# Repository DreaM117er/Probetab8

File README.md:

# Probetab8

|||
|--|--|
|||

## 說明

Probetab8是一把在設計途中不斷地向Google Gemini諮詢電路學知識的一把迷你鍵盤，是我用來進一步地學習電路學的一個巨大突破的成果。

這把鍵盤有以下幾個特點：
1. 晶片核心爲RP2040，全引腳輸出。
2. 可以燒錄RP2040 Debug Probe官方的韌體。
3. 可以按照我設計的佈局設置需要的功能：4+4顆按鍵、4按鍵+1旋鈕、2旋鈕。
4. 搭載Azoteq TPS65觸控板。
5. QMK/VIAL韌體。

## 使用材料

|||
|--|--|

### 電子元件

|類型|名稱|數量|封裝|備註|Reference|
|--|--|--|--|--|--|
|MCU|RP2040|1|QFN-56|-|U3|
|ESD|SRV05-4|1|SOT-23-6|-|U1|
|LDO|RT9013-33GB|1|SOT-23-5|-|U2|
|QSPI|W25Q128JVS|1|SOIC-8|-|U4|
|Resonator|Crystal|1|SMD-3225-4Pin|-|Y1|
|Receptacle|USB-C|1|-|16Pin|-|
|Fuse|6V, 500mA|1|0805|-|F1|
|SW|-|1|SPST_TL3342|BOOT||
|Capacitor|1uF|4|0603|-|C1, C2, C8, C16|
|Capacitor|15pF|2|0603|-|C3, C4|
|Capacitor|100nF|10|0603|-|C5-C7, C9-C15|
|Resistor|5.1K|2|0603|-|R1, R2|
|Resistor|27R|2|0603|-|R3, R4|
|Resistor|10K|2|0603|-|R5, R7|
|Resistor|1K|1|0603|-|R6|
|Resistor|470R|2|0603|-|R8, R9|
|Resistor|220R|1|0603|-|R10|
|Module|TPS65-201A-S|1|-|-|-|
|Cable|FFC-0.5mm|1|6Pin|L: 100mm|-|
|Socket|FFC-0.5mm|1|FH12-6S-0.5SH 6Pin|-|-|
|RED|LED|3|0603|After R8-10|-|

### 機構元件

|名稱|規格|數量|備註|
|--|--|--|--|
|Screw|M2x4mm|4|扁頭|
|Screw|M2x6mm|2|扁頭|
|Screw|M2x8mm|2|扁頭|
|Case|上蓋|1|-|
|Case|下蓋|1|-|
|Feets|8x1mm|4|矽膠腳貼|

### 自由選擇

|名稱|規格|數量|備註|
|--|--|--|--|
|按鍵|Choc v1, GLP1.0-2.0|0-8|-|
|鍵帽|Choc v1, MX stem for LP|0-8|-|
|編碼器|EC-11|0-2|L: 10mm、A: 5.5-5.0mm, 半軸 D型|

## 注意事項

- 不提供CSV給大家使用，如果需要PCBA，請自行修改PCB檔案。因爲這把鍵盤屬於純手工焊接，挑戰自己的焊接技巧，成果就是你的。
- 外殼上蓋有分4種，分別應對自由選擇的元件使用，底殼通用。
- 外殼檔案及PCB檔案都開放給大家，要修正改造請按照開源相關規定，我就不再說明了。 
- 焊接的時候，特別注意預熱、加熱相關的技巧及熟悉度，以免燒壞MCU或是燙傷；還有注意環境通風。
- 關於Jumper：

    - Status LED：測試燈開關，測試沒問題可移除。
    - TPS65模組：RDY及RST，有使用這兩個引腳再焊接。

## 軟體工具

- Fusion。
- KiCAD 9.0.2。
- VScode。
- QMK、VIAL。
- Resberry官方Debug Probe韌體。

## 硬體工具

- TS-100、TS-101。
- MPH-30。
- FDM列印機。
- 萬用電表。

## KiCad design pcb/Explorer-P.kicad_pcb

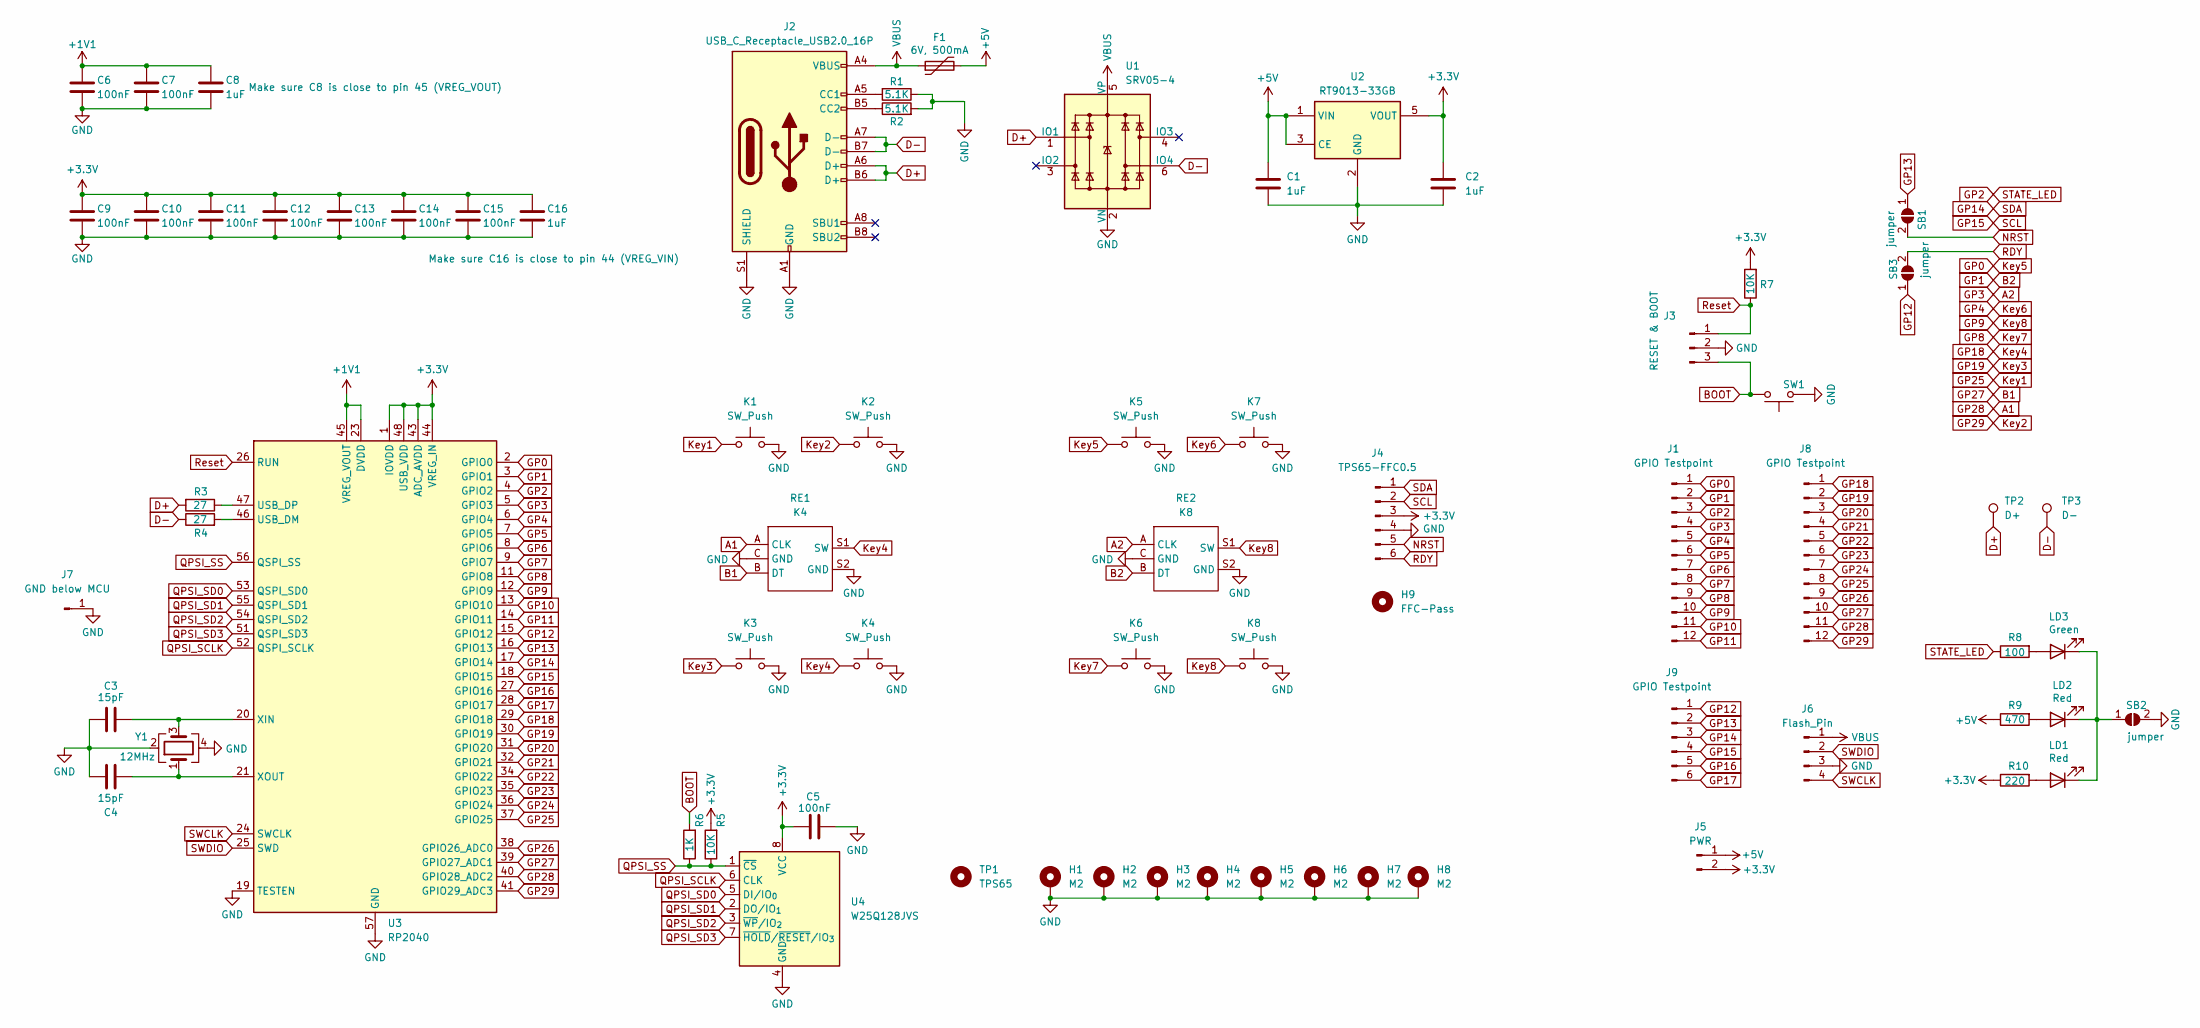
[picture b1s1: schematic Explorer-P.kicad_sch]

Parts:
C1, C2: 1uF; R_0603_1608Metric
C3, C4: 15pF; R_0603_1608Metric
C5: 100nF; R_0603_1608Metric
C6, C7, C9, C10, C11, C12, C13, C14, C15: 100nF; R_0603_1608Metric; MFR. Part # CL05B104KB54PNC
C8, C16: 1uF; R_0603_1608Metric; MFR. Part # CL05A105KA5NQNC
F1: 6V, 500mA; C_0805_2012Metric_Pad1.18x1.45mm_HandSolder; LCSC C269104
H1, H2, H3, H4, H5, H6, H7, H8: M2; MountingHole_2.2mm_M2_DIN965_Pad
H9: FFC-Pass; MountingHole_2.2mm_M2
J1, J8: GPIO Testpoint; Testpoint_2.54mm_01x12_1to2_Hole2Pad
J2: USB_C_Receptacle_USB2.0_16P; USB_C_Receptacle_G-Switch_GT-USB-7010ASV
J3: RESET & BOOT; PinHeader_1x03_P2.54mm_Vertical
J4: TPS65-FFC0.5; Hirose_FH12-6S-0.5SH_1x06-1MP_P0.50mm_Horizontal
J5: PWR; Testpoint_2.54mm_01x02_1to2_Hole2Pad
J6: Flash_Pin; PinHeader_1x04_P2.54mm_Vertical
J7: GND below MCU; MountingHole_2.2mm_M2_DIN965_Pad
J9: GPIO Testpoint; Testpoint_2.54mm_01x06_1to2_Hole2Pad
K1, K2, K3, K4, K5, K6, K7, K8: SW_Push; SW_Choc_GLP_KLP12_THT2
LD1, LD2: Red; LED_0603_1608Metric; MFR. Part # 19-217/GHC-YR1S2/3T; LCSC C72043
LD3: Green; LED_0603_1608Metric; MFR. Part # 19-217/GHC-YR1S2/3T; LCSC C72043
R1, R2: 5.1K; R_0603_1608Metric
R3, R4: 27; R_0603_1608Metric
R5, R7: 10K; R_0603_1608Metric
R6: 1K; R_0603_1608Metric
R8: 100; R_0603_1608Metric; MFR. Part # 0402WGF1001TCE
R9: 470; R_0603_1608Metric; MFR. Part # 0402WGF1001TCE
R10: 220; R_0603_1608Metric; MFR. Part # 0402WGF1001TCE
RE1: K4; RotaryEncoder_EC11
RE2: K8; RotaryEncoder_EC11
SB1, SB2, SB3: jumper; SolderJumper-2_P1.3mm_Open_TrianglePad1.0x1.5mm
SW1: BOOT; SW_SPST_TL3342
TP1: TPS65; Azoteq_TPS65_201A_S
TP2: D+; TestPoint_Pad_2.5x2.5mm
TP3: D-; TestPoint_Pad_2.5x2.5mm
U1: SRV05-4; SOT-23-6
U2: RT9013-33GB; SOT-23-5; LCSC C47773
U3: RP2040; QFN-56-1EP_7x7mm_P0.4mm_EP3.2x3.2mm; LCSC C2040
U4: W25Q128JVS; SOIC-8_5.3x5.3mm_P1.27mm; LCSC C97521
Y1: 12MHz; Crystal_SMD_3225-4Pin_3.2x2.5mm; LCSC C9002

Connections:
+1V1: C6.1, C7.1, C8.1, U3.23 (DVDD), U3.45 (VREG_VOUT), U3.50 (DVDD)
+3.3V: C2.1, C5.1, C9.1, C10.1, C11.1, C12.1, C13.1, C14.1, C15.1, C16.1, J4.3, J5.2, R5.2, R7.2, R10.1, U2.5 (VOUT), U3.1 (IOVDD), U3.10 (IOVDD), U3.22 (IOVDD), U3.33 (IOVDD), U3.42 (IOVDD), U3.43 (ADC_AVDD), U3.44 (VREG_IN), U3.48 (USB_VDD), U3.49 (IOVDD), U4.8 (VCC)
+5V: C1.2, F1.2, J5.1, R9.1, U2.1 (VIN), U2.3 (CE)
A1: J8.11, RE1.A (CLK), U3.40 (GPIO28_ADC2)
A2: J1.4, RE2.A (CLK), U3.5 (GPIO3)
B1: J8.10, RE1.B (DT), U3.39 (GPIO27_ADC1)
B2: J1.2, RE2.B (DT), U3.3 (GPIO1)
BOOT: J3.3, R6.2, SW1.2
D+: J2.A6 (D+), J2.B6 (D+), R3.2, TP2.1, U1.1 (IO1)
D-: J2.A7 (D-), J2.B7 (D-), R4.1, TP3.1, U1.6 (IO4)
GND: C1.1, C2.2, C3.2, C4.2, C5.2, C6.2, C7.2, C8.2, C9.2, C10.2, C11.2, C12.2, C13.2, C14.2, C15.2, C16.2, H1.1, H2.1, H3.1, H4.1, H5.1, H6.1, H7.1, H8.1, J2.A1 (GND), J2.A12 (GND), J2.B1 (GND), J2.B12 (GND), J2.S1 (SHIELD), J3.2, J4.4, J6.3, J7.1, K1.2, K2.2, K3.2, K4.2, K5.2, K6.2, K7.2, K8.2, R1.1, R2.2, RE1.C (GND), RE1.S2 (GND), RE2.C (GND), RE2.S2 (GND), SB2.2 (B), SW1.1, U1.2 (VN), U2.2 (GND), U3.19 (TESTEN), U3.57 (GND), U4.4 (GND), Y1.2, Y1.4
GP0: J1.1, K5.1, U3.2 (GPIO0)
GP2: J1.3, R8.1, U3.4 (GPIO2)
GP4: J1.5, K7.1, U3.6 (GPIO4)
GP5: J1.6, U3.7 (GPIO5)
GP6: J1.7, U3.8 (GPIO6)
GP7: J1.8, U3.9 (GPIO7)
GP8: J1.9, K6.1, U3.11 (GPIO8)
GP9: J1.10, K8.1, RE2.S1 (SW), U3.12 (GPIO9)
GP10: J1.11, U3.13 (GPIO10)
GP11: J1.12, U3.14 (GPIO11)
GP12: J9.1, SB3.1 (A), U3.15 (GPIO12)
GP13: J9.2, SB1.1 (A), U3.16 (GPIO13)
GP14: J4.1, J9.3, U3.17 (GPIO14)
GP15: J4.2, J9.4, U3.18 (GPIO15)
GP16: J9.5, U3.27 (GPIO16)
GP17: J9.6, U3.28 (GPIO17)
GP18: J8.1, K4.1, RE1.S1 (SW), U3.29 (GPIO18)
GP19: J8.2, K3.1, U3.30 (GPIO19)
GP20: J8.3, U3.31 (GPIO20)
GP21: J8.4, U3.32 (GPIO21)
GP22: J8.5, U3.34 (GPIO22)
GP23: J8.6, U3.35 (GPIO23)
GP24: J8.7, U3.36 (GPIO24)
GP25: J8.8, K1.1, U3.37 (GPIO25)
GP26: J8.9, U3.38 (GPIO26_ADC0)
GP29: J8.12, K2.1, U3.41 (GPIO29_ADC3)
NRST: J4.5, SB1.2 (B)
unnamed: J2.A5 (CC1), R1.2
unnamed: J2.B5 (CC2), R2.1
unnamed: LD1.2 (A), R10.2
unnamed: LD1.1 (K), LD2.1 (K), LD3.1 (K), SB2.1 (A)
unnamed: LD2.2 (A), R9.2
unnamed: LD3.2 (A), R8.2
unnamed: R4.2, U3.46 (USB_DM)
unnamed: R3.1, U3.47 (USB_DP)
unnamed: C3.1, U3.20 (XIN), Y1.3
unnamed: C4.1, U3.21 (XOUT), Y1.1
QPSI_SCLK: U3.52 (QSPI_SCLK), U4.6 (CLK)
QPSI_SD0: U3.53 (QSPI_SD0), U4.5 (DI/IO_{0})
QPSI_SD1: U3.55 (QSPI_SD1), U4.2 (DO/IO_{1})
QPSI_SD2: U3.54 (QSPI_SD2), U4.3 (~WP/IO_{2})
QPSI_SD3: U3.51 (QSPI_SD3), U4.7 (~HOLD/~RESET/IO_{3})
QPSI_SS: R5.1, R6.1, U3.56 (QSPI_SS), U4.1 (~CS)
RDY: J4.6, SB3.2 (B)
Reset: J3.1, R7.1, U3.26 (RUN)
SWCLK: J6.4, U3.24 (SWCLK)
SWDIO: J6.2, U3.25 (SWD)
VBUS: F1.1, J2.A4 (VBUS), J2.A9 (VBUS), J2.B4 (VBUS), J2.B9 (VBUS), J6.1, U1.5 (VP)

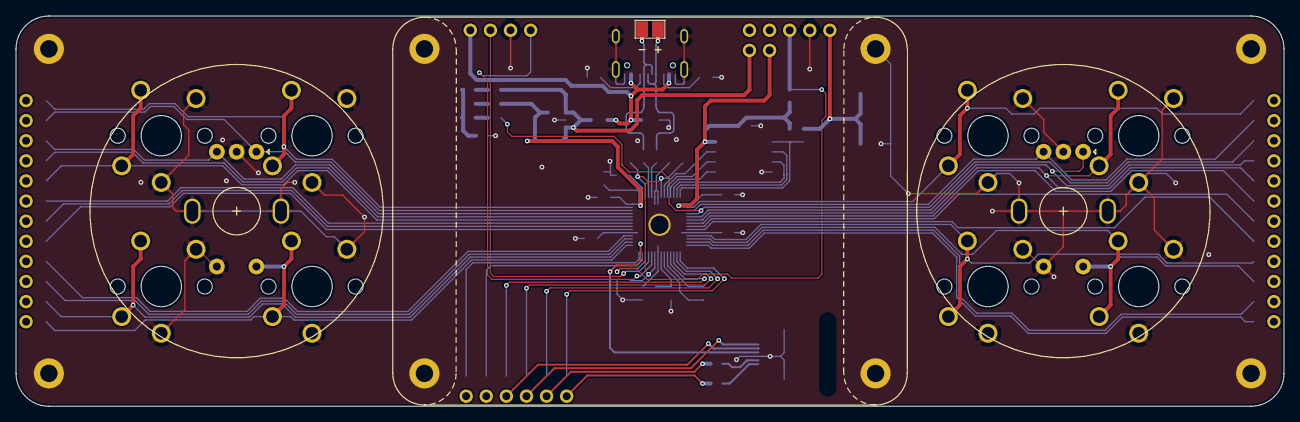
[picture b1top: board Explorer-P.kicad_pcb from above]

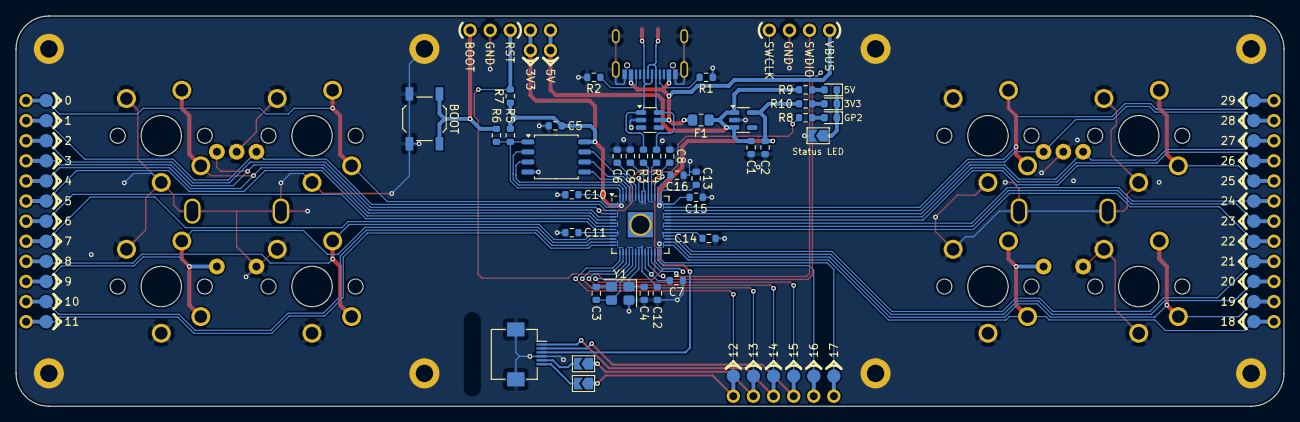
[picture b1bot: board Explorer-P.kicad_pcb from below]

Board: 2 copper layers, 160.2 x 49.3 mm, 70 parts (47 on the bottom side), 59 nets.

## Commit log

2025-08-13 add file
2025-08-15 add notes on sch file
2025-10-26 rebuild readme.md
2025-10-27 enew readme & update case
